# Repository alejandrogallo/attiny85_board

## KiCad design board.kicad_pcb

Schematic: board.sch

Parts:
C1: 22p; C_0805_HandSoldering
D1: D; D_0805
D2: LED; LED_1206
IC1: ATTINY85-P; DIP-8_W10.16mm
P1: USB_OTG; USB_Micro-B_10103594-0001LF
P2, P3: CONN_01X04; Socket_Strip_Straight_1x04
P4: USBasp; Pin_Header_Straight_2x05
R1: 200; R_0603_HandSoldering
SW1: SW_PUSH; SW_SPST_FSMSM

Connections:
+5V: C1.1, D2.2, IC1.8 (VCC), P1.1, P3.1, P4.2
/PB0: IC1.5 (PB0(MOSI/DI/SDA/AIN0/OC0A/OC1A/AREF/PCI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), P3.4, P4.1
/PB1: IC1.6 (PB1(MISO/DO/AIN1/OC0B/OC1A/PCINT1)), P3.3, P4.9
/PB2: IC1.7 (PB2(SCK/USCK/SCL/T0/INT0/ADC1/PCINT2)), P3.2, P4.7
/PB3: IC1.2 (PB3(XTAL1/CLKI/OC1B/ADC3/PCINT3)), P2.2
/PB4: IC1.3 (PB4(XTAL2/CLKO/OC1B/ADC2/PCINT4)), P2.3
/PB5: D1.2, IC1.1 (PB5(~RESET~/dW/ADC0/PCINT5)), P2.1, P4.5
GND: C1.2, IC1.4 (GND), P1.5, P1.6, P2.4, P4.4, P4.6, P4.8, P4.10, SW1.2
unnamed: D1.1, R1.1, SW1.1
unnamed: D2.1, R1.2

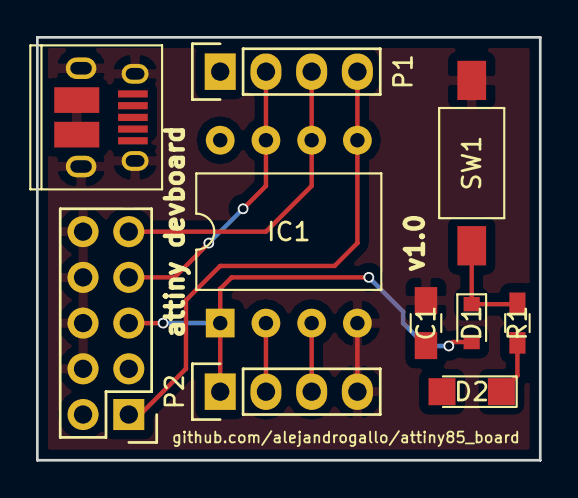
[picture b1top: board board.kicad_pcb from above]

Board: 2 copper layers, 27.9 x 23.5 mm, 10 parts (0 on the bottom side), 10 nets.

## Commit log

2018-01-17 Annotate
2018-01-17 Add footprints
2018-01-18 Add lib symbols
2018-01-18 add pcb
2018-01-18 Connect push button
2018-01-18 Add some routing
2018-01-18 Add GND and VCC covers
